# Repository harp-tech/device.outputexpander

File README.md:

## Harp Output Expander
Harp board to expand the outputs of the current harp ecosystem.

### Key Features ###

* TBA

### Connectivity ###

* TBA

## Interface ##

The interface with the Harp Output Expander can be done through [Bonsai](https://bonsai-rx.org/).

## Licensing ##

Each subdirectory will contain a license or, possibly, a set of licenses if it involves both hardware and software.

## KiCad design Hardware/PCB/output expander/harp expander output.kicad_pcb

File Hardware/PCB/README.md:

# Harp Expander PCB

## Licensing

The designs, documentation, and photos available in this repository are free: you can redistribute it and/or modify it under the terms of the used license.
Check file named LICENSE.

Copyright Filipe Carvalho 2020-2026

<br />This work is licensed under a <a rel="license" href="http://creativecommons.org/licenses/by-nc-sa/3.0/igo/">Creative Commons Attribution-NonCommercial-ShareAlike 3.0 IGO License</a>.

If your are interested in obtaining a license to sell this device, please contact filipe@open-ephys.org

[1]: https://docs.google.com/spreadsheets/d/1aobmmEzBDethzIlrm1eg0eYkBqlyX3s9WbA9KgRwVQI/edit?usp=sharing

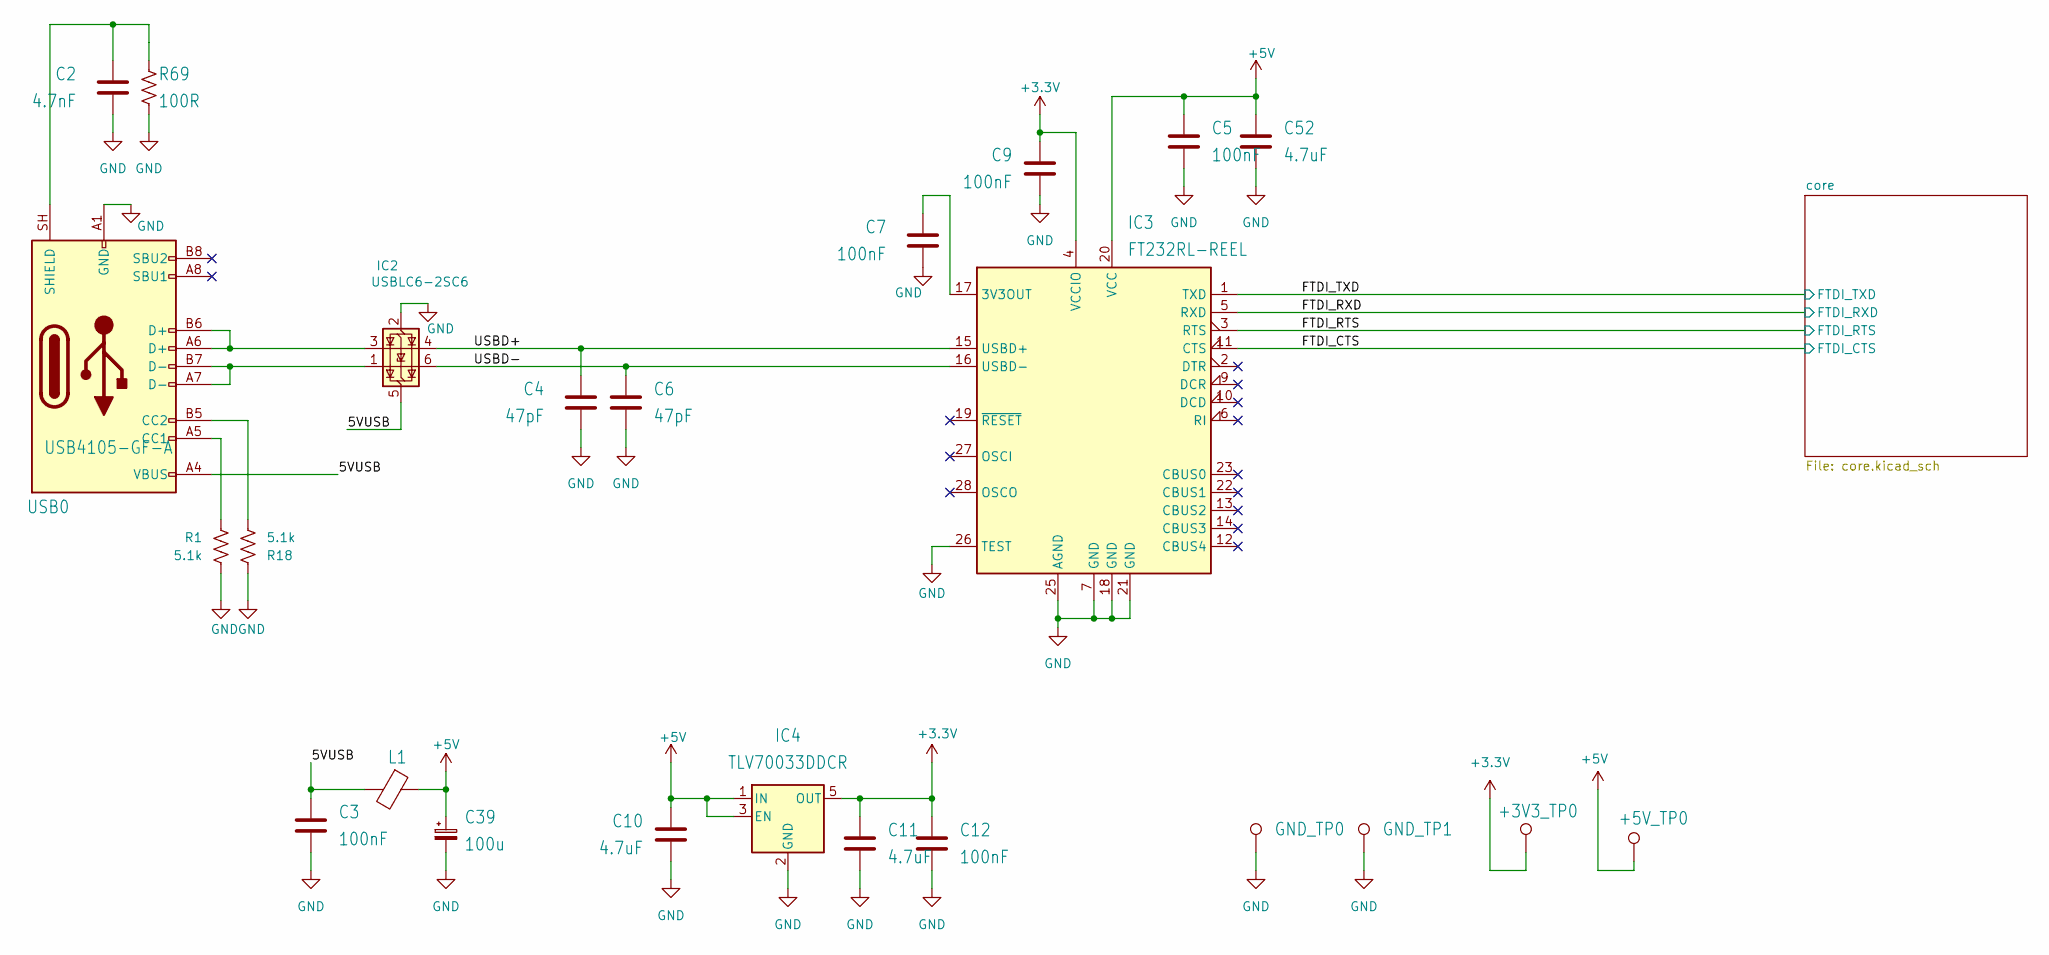
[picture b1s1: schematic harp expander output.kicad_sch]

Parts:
+3V3_TP0, +5V_TP0: TPPAD1-13; TestPoint_Loop_D1.80mm_Drill1.0mm_Beaded; MPN n.a.
C2: 4.7nF; C_0402_1005Metric; Tolerance 10%; Voltage 100V; MPN 885012205084
C3, C5, C7, C9, C12: 100nF; C_0402_1005Metric; Tolerance 10%; Voltage 50V; MPN CGA2B3X7R1H104K050BB
C4, C6: 47pF; C_0402_1005Metric; Tolerance 5%; Voltage 50V; MPN 04025A470JAT2A
C10, C11, C52: 4.7uF; C_0603_1608Metric; Tolerance 10%; Voltage 16V; MPN C1608X6S1C475K080AC
C39: 100u; CP_Radial_D6.3mm_P2.50mm; Tolerance 20%; Voltage 25V; MPN EEU-FM1E101B
GND_TP0, GND_TP1: TPPAD1-13; TestPoint_Loop_D1.80mm_Drill1.0mm_Beaded; MPN n.a.
IC2: USBLC6-2SC6; SOT-23-6; MPN USBLC6-2SC6
IC3: FT232RL-REEL; SSOP-28_5.3x10.2mm_P0.65mm; MPN FT232RL-REEL
IC4: TLV70033DDCR; SOT-23-5; MPN TLV70033DDCR
L1: MI0805K400R-10; R_0805_2012Metric; MPN MI0805K400R-10
R1, R18: 5.1k; R_0402_1005Metric; Tolerance 1%; MPN ERJ-2RKF5101X
R69: 100R; R_0603_1608Metric; Tolerance 1%; MPN CRCW0603100RFKEAHP
USB0: USB4105-GF-A; USB_C_Receptacle_GCT_USB4105-xx-A_16P_TopMnt_Horizontal; MPN USB4105-GF-A

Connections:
+3.3V: +3V3_TP0.1 (1_1), C9.1, C11.1, C12.1, IC3.4 (VCCIO), IC4.5 (OUT); also elsewhere on the board
+5V: +5V_TP0.1 (1_1), C5.1, C10.1, C39.1, C52.1, IC3.20 (VCC), IC4.1 (IN), IC4.3 (EN), L1.1; also elsewhere on the board
/5VUSB: C3.1, IC2.5 (VBUS), L1.2, USB0.A4 (VBUS), USB0.A9 (VBUS), USB0.B4 (VBUS), USB0.B9 (VBUS)
/FTDI_CTS: IC3.11 (CTS); also elsewhere on the board
/FTDI_RTS: IC3.3 (RTS); also elsewhere on the board
/FTDI_RXD: IC3.5 (RXD); also elsewhere on the board
/FTDI_TXD: IC3.1 (TXD); also elsewhere on the board
/USBD+: C4.1, IC2.4 (I/O2), IC3.15 (USBD+)
/USBD-: C6.1, IC2.6 (I/O1), IC3.16 (USBD-)
GND: C2.2, C3.2, C4.2, C5.2, C6.2, C7.2, C9.2, C10.2, C11.2, C12.2, C39.2, C52.2, GND_TP0.1 (1_1), GND_TP1.1 (1_1), IC2.2 (GND), IC3.7 (GND), IC3.18 (GND), IC3.21 (GND), IC3.25 (AGND), IC3.26 (TEST), IC4.2 (GND), R1.2, R18.1, R69.1, USB0.A1 (GND), USB0.A12 (GND), USB0.B1 (GND), USB0.B12 (GND); also elsewhere on the board
unnamed: IC2.1 (I/O1), USB0.A7 (D-), USB0.B7 (D-)
unnamed: IC2.3 (I/O2), USB0.A6 (D+), USB0.B6 (D+)
unnamed: C7.1, IC3.17 (3V3OUT)
unnamed: R1.1, USB0.A5 (CC1)
unnamed: R18.2, USB0.B5 (CC2)
unnamed: C2.1, R69.2, USB0.SH (SHIELD)

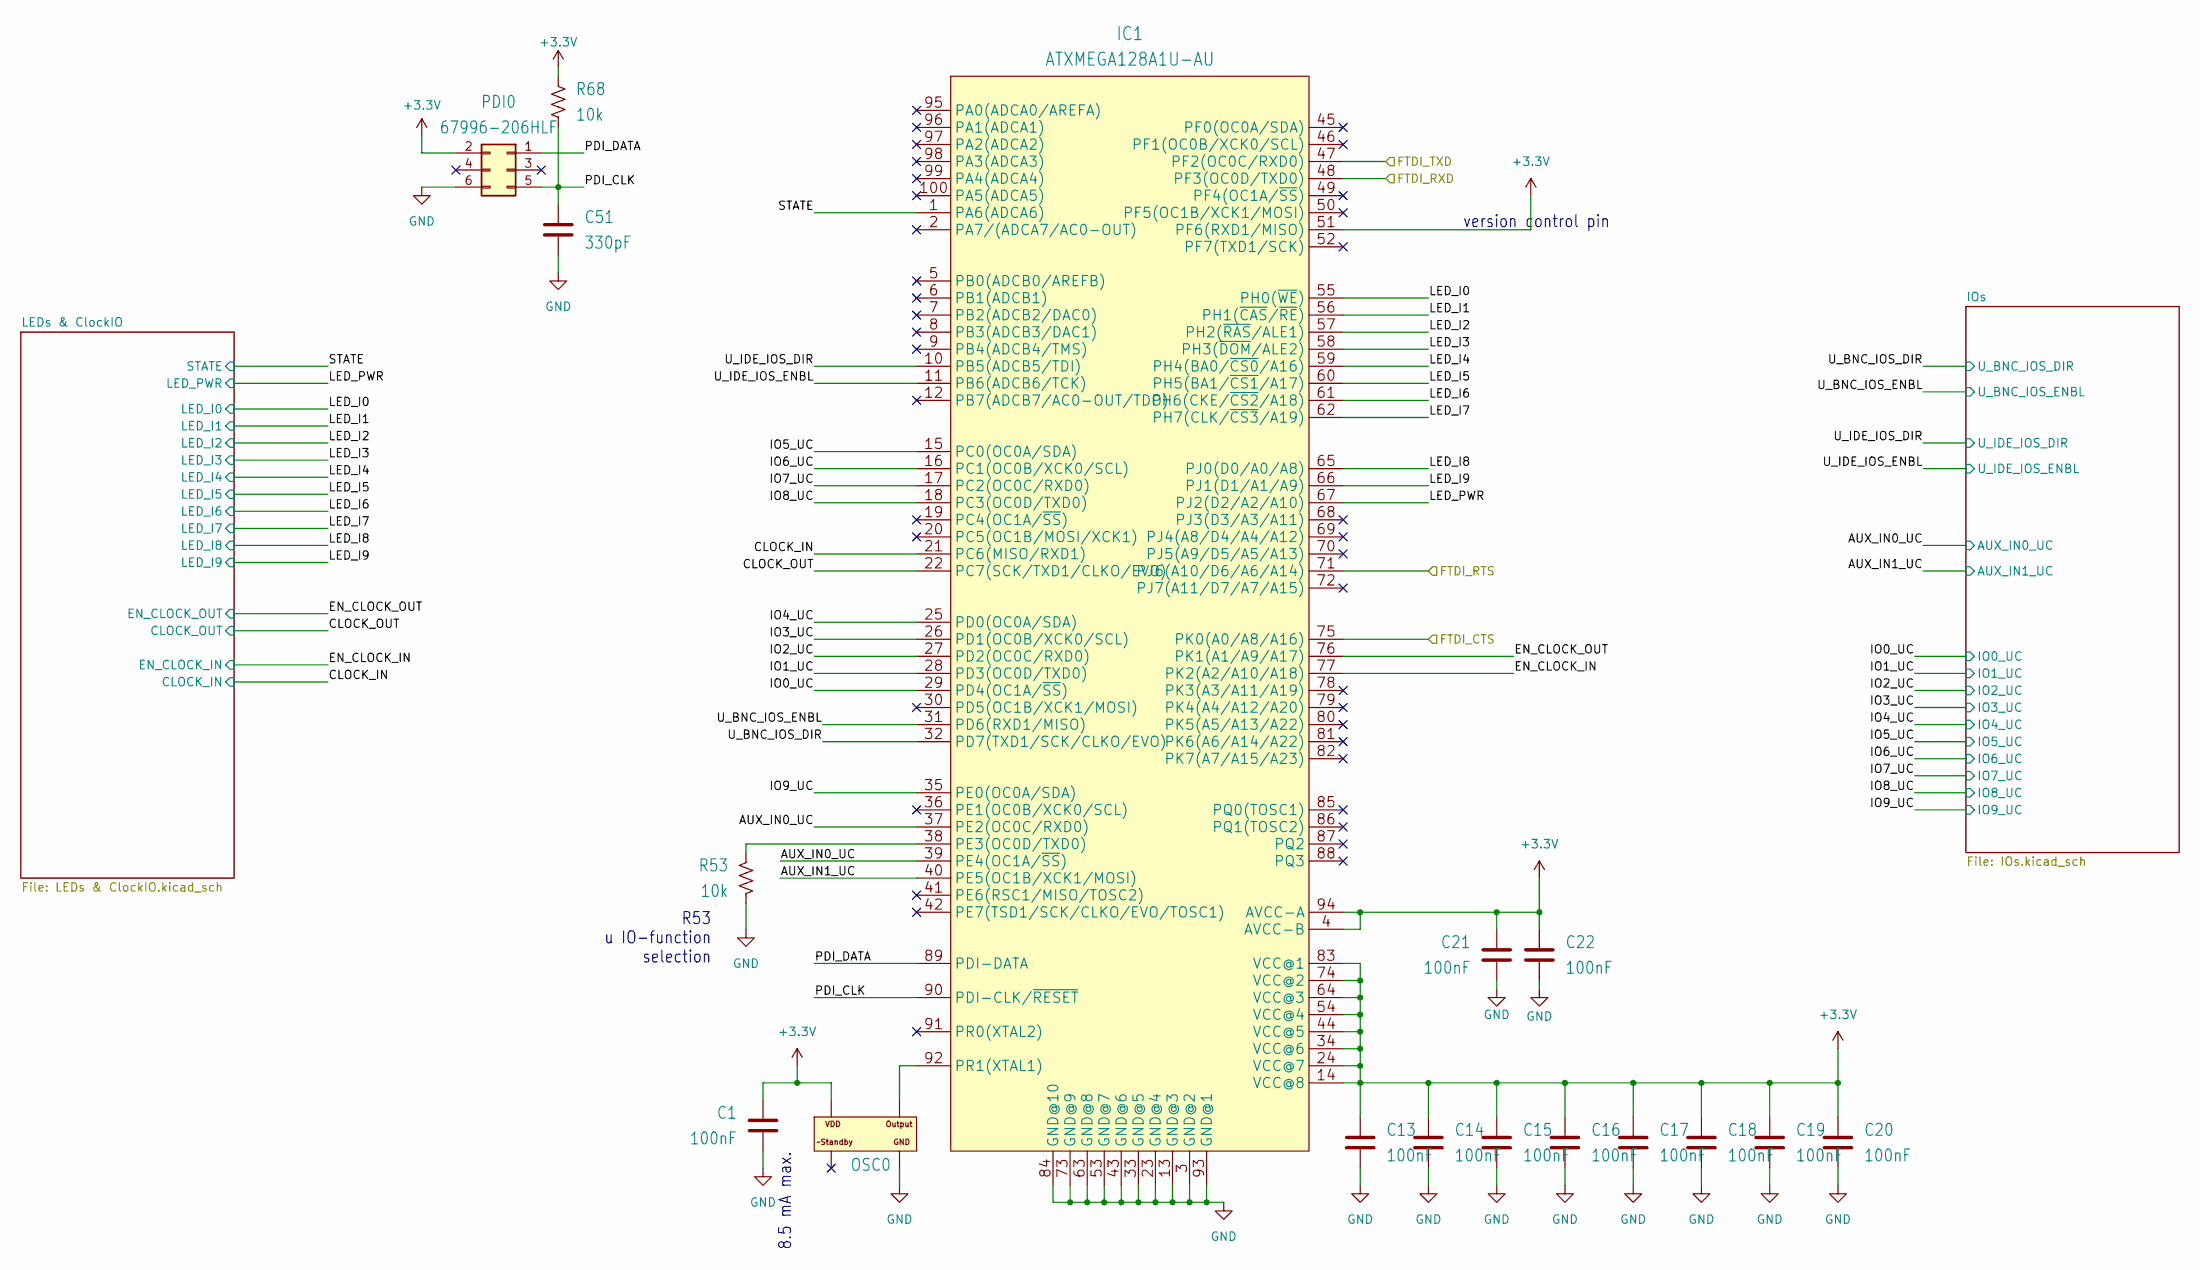
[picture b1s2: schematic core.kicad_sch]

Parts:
C1, C13, C14, C15, C16, C17, C18, C19, C20, C21, C22: 100nF; C_0402_1005Metric; Tolerance 10%; Voltage 50V; MPN CGA2B3X7R1H104K050BB
C51: 330pF; C_0402_1005Metric; Tolerance 5%; Voltage 50V; MPN C0402C331J5GAC7867
IC1: ATXMEGA128A1U-AU; TQFP-100_14x14mm_P0.5mm; MPN ATXMEGA128A1U-AU
OSC0: O 32,0-JT32C-A-K-3,3-LF; OSCILLATOR_3.2X2.5; MPN O 32,0-JT32C-A-K-3,3-LF
PDI0: 67996-206HLF; PinHeader_2x03_P2.54mm_Vertical; MPN 67996-206HLF
R53, R68: 10k; R_0402_1005Metric; Tolerance 1%; MPN CRCW040210K0FKED

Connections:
+3.3V: C1.1, C13.1, C14.1, C15.1, C16.1, C17.1, C18.1, C19.1, C20.1, C21.1, C22.1, IC1.4 (AVCC-B), IC1.14 (VCC@8), IC1.24 (VCC@7), IC1.34 (VCC@6), IC1.44 (VCC@5), IC1.51 (PF6(RXD1/MISO)), IC1.54 (VCC@4), IC1.64 (VCC@3), IC1.74 (VCC@2), IC1.83 (VCC@1), IC1.94 (AVCC-A), OSC0.4 (VDD), PDI0.2, R68.2; also elsewhere on the board
/FTDI_CTS: IC1.75 (PK0(A0/A8/A16)); also elsewhere on the board
/FTDI_RTS: IC1.71 (PJ6(A10/D6/A6/A14)); also elsewhere on the board
/FTDI_RXD: IC1.48 (PF3(OC0D/TXD0)); also elsewhere on the board
/FTDI_TXD: IC1.47 (PF2(OC0C/RXD0)); also elsewhere on the board
/core/AUX_IN0_UC: IC1.37 (PE2(OC0C/RXD0)), IC1.39 (PE4(OC1A/~SS)); also elsewhere on the board
/core/AUX_IN1_UC: IC1.40 (PE5(OC1B/XCK1/MOSI)); also elsewhere on the board
/core/CLOCK_IN: IC1.21 (PC6(MISO/RXD1)); also elsewhere on the board
/core/CLOCK_OUT: IC1.22 (PC7(SCK/TXD1/CLKO/EVO)); also elsewhere on the board
/core/EN_CLOCK_IN: IC1.77 (PK2(A2/A10/A18)); also elsewhere on the board
/core/EN_CLOCK_OUT: IC1.76 (PK1(A1/A9/A17)); also elsewhere on the board
/core/IO0_UC: IC1.29 (PD4(OC1A/~SS)); also elsewhere on the board
/core/IO1_UC: IC1.28 (PD3(OC0D/TXD0)); also elsewhere on the board
/core/IO2_UC: IC1.27 (PD2(OC0C/RXD0)); also elsewhere on the board
/core/IO3_UC: IC1.26 (PD1(OC0B/XCK0/SCL)); also elsewhere on the board
/core/IO4_UC: IC1.25 (PD0(OC0A/SDA)); also elsewhere on the board
/core/IO5_UC: IC1.15 (PC0(OC0A/SDA)); also elsewhere on the board
/core/IO6_UC: IC1.16 (PC1(OC0B/XCK0/SCL)); also elsewhere on the board
/core/IO7_UC: IC1.17 (PC2(OC0C/RXD0)); also elsewhere on the board
/core/IO8_UC: IC1.18 (PC3(OC0D/TXD0)); also elsewhere on the board
/core/IO9_UC: IC1.35 (PE0(OC0A/SDA)); also elsewhere on the board
/core/LED_I0: IC1.55 (PH0(~WE)); also elsewhere on the board
/core/LED_I1: IC1.56 (PH1(~CAS/~RE)); also elsewhere on the board
/core/LED_I2: IC1.57 (PH2(~RAS/ALE1)); also elsewhere on the board
/core/LED_I3: IC1.58 (PH3(~DOM/ALE2)); also elsewhere on the board
/core/LED_I4: IC1.59 (PH4(BA0/~CS0/A16)); also elsewhere on the board
/core/LED_I5: IC1.60 (PH5(BA1/~CS1/A17)); also elsewhere on the board
/core/LED_I6: IC1.61 (PH6(CKE/~CS2/A18)); also elsewhere on the board
/core/LED_I7: IC1.62 (PH7(CLK/~CS3/A19)); also elsewhere on the board
/core/LED_I8: IC1.65 (PJ0(D0/A0/A8)); also elsewhere on the board
/core/LED_I9: IC1.66 (PJ1(D1/A1/A9)); also elsewhere on the board
/core/LED_PWR: IC1.67 (PJ2(D2/A2/A10)); also elsewhere on the board
/core/PDI_CLK: C51.1, IC1.90 (PDI-CLK/~RESET), PDI0.5, R68.1
/core/PDI_DATA: IC1.89 (PDI-DATA), PDI0.1
/core/STATE: IC1.1 (PA6(ADCA6)); also elsewhere on the board
/core/U_BNC_IOS_DIR: IC1.32 (PD7(TXD1/SCK/CLKO/EVO)); also elsewhere on the board
/core/U_BNC_IOS_ENBL: IC1.31 (PD6(RXD1/MISO)); also elsewhere on the board
/core/U_IDE_IOS_DIR: IC1.10 (PB5(ADCB5/TDI)); also elsewhere on the board
/core/U_IDE_IOS_ENBL: IC1.11 (PB6(ADCB6/TCK)); also elsewhere on the board
GND: C1.2, C13.2, C14.2, C15.2, C16.2, C17.2, C18.2, C19.2, C20.2, C21.2, C22.2, C51.2, IC1.3 (GND@2), IC1.13 (GND@3), IC1.23 (GND@4), IC1.33 (GND@5), IC1.43 (GND@6), IC1.53 (GND@7), IC1.63 (GND@8), IC1.73 (GND@9), IC1.84 (GND@10), IC1.93 (GND@1), OSC0.2 (GND), PDI0.6, R53.2; also elsewhere on the board
unnamed: IC1.38 (PE3(OC0D/TXD0)), R53.1
unnamed: IC1.92 (PR1(XTAL1)), OSC0.3 (OUTPUT)

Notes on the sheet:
8.5 mA max.
R53 u IO-function selection
version control pin

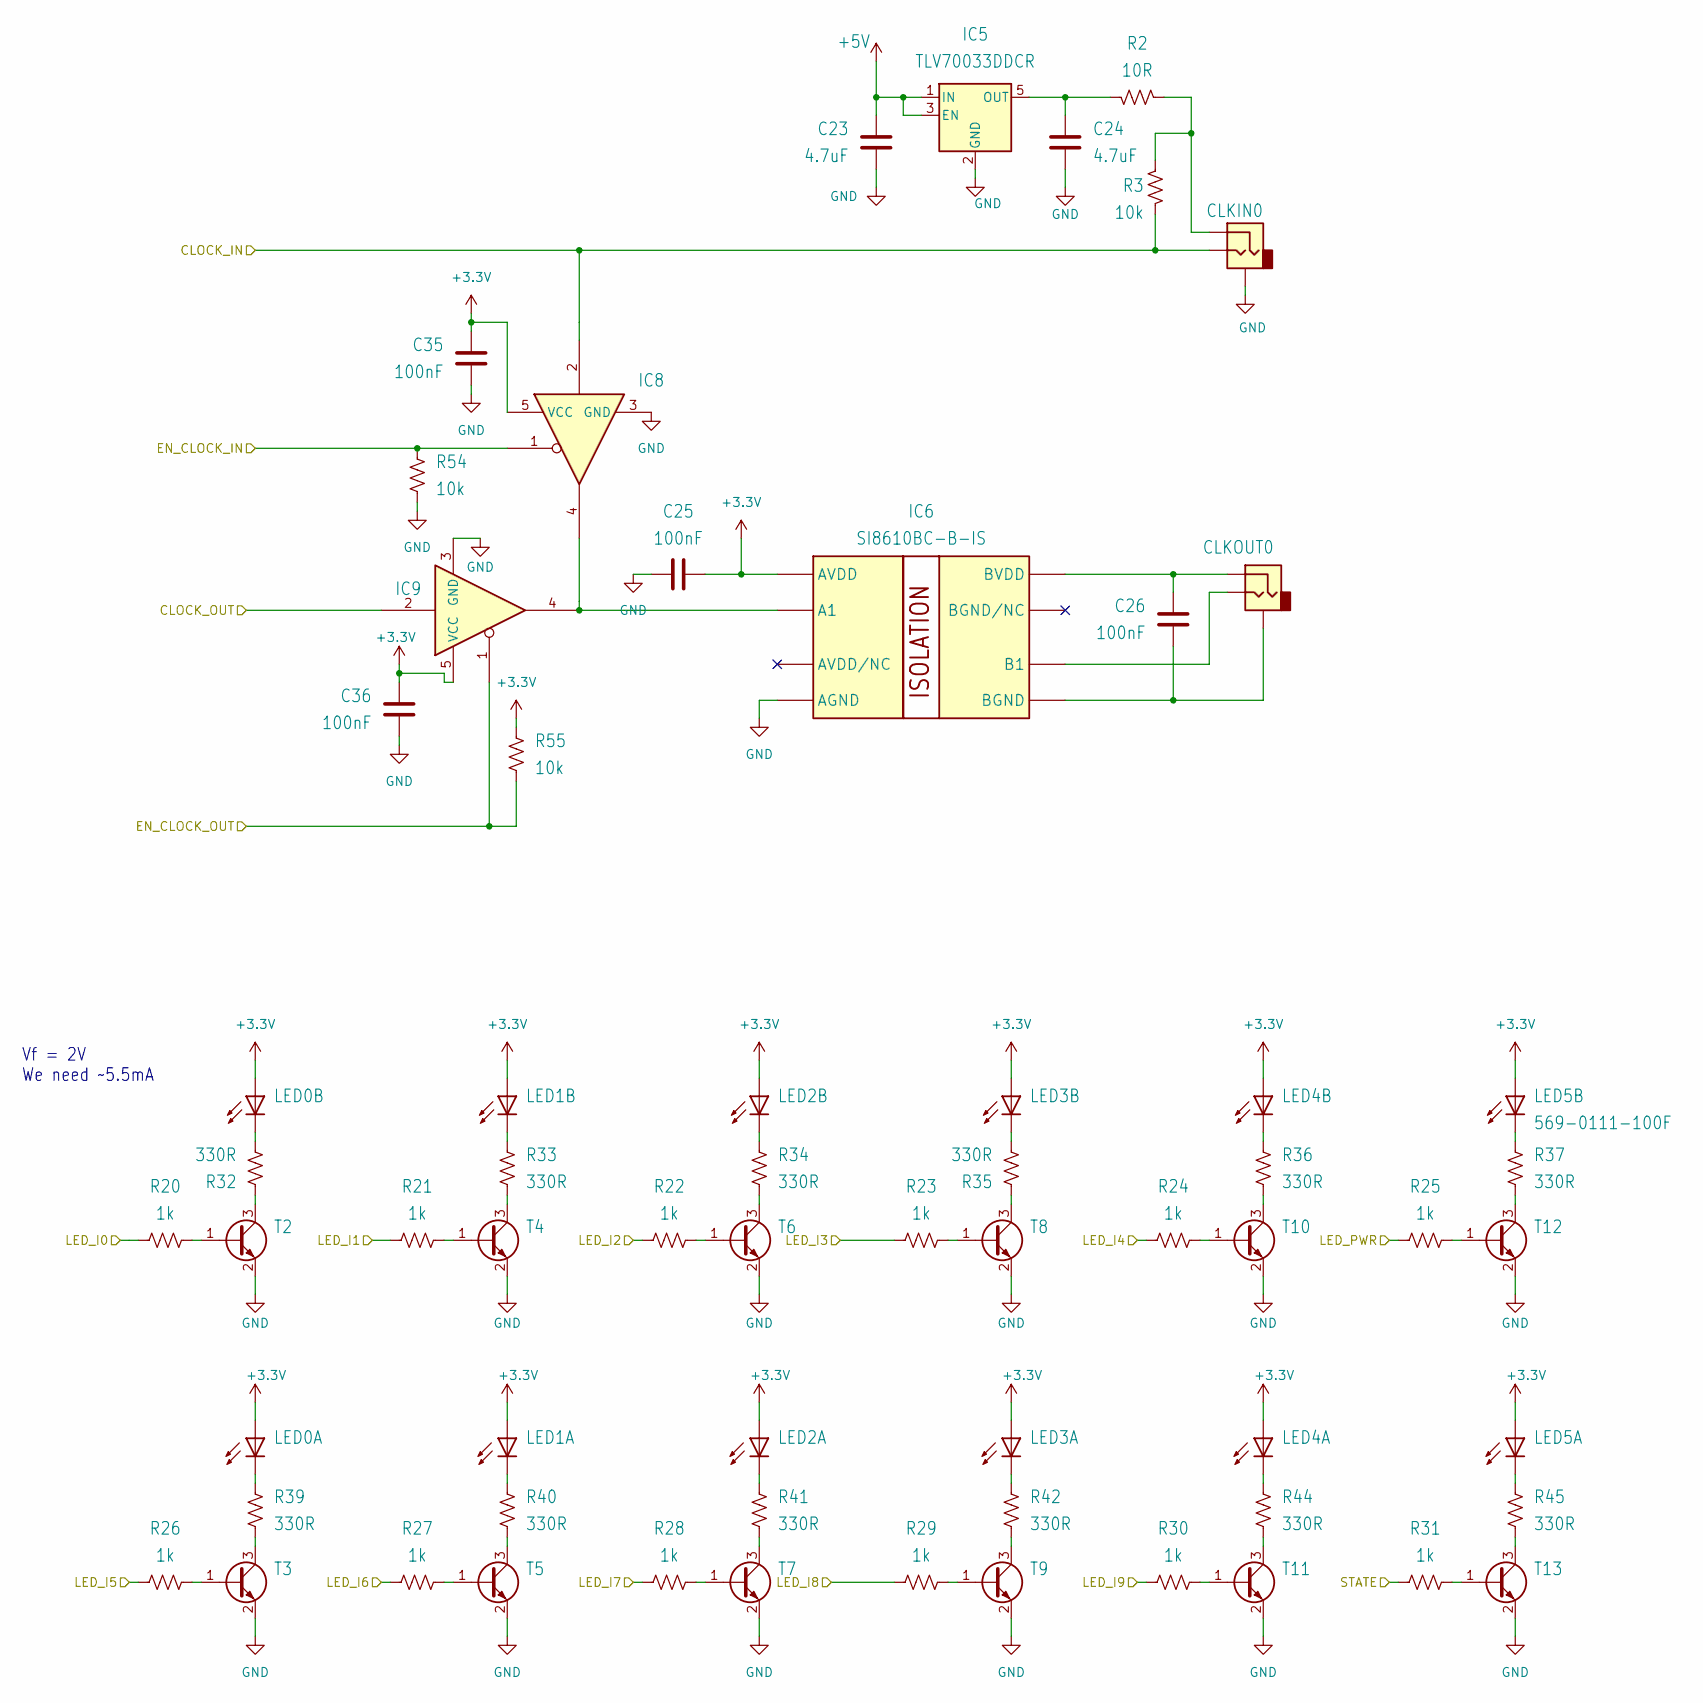
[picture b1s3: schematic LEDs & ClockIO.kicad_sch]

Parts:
C23, C24: 4.7uF; C_0603_1608Metric; Tolerance 10%; Voltage 16V; MPN C1608X6S1C475K080AC
C25, C26, C35, C36: 100nF; C_0402_1005Metric; Tolerance 10%; Voltage 50V; MPN CGA2B3X7R1H104K050BB
CLKIN0: 35RASMT2BHNTRX; MPN 35RASMT2BHNTRX
CLKOUT0: 35RASMT2BHNTRX; MPN 35RASMT2BHNTRX
IC5: TLV70033DDCR; SOT-23-5; MPN TLV70033DDCR
IC6: SI8610BC-B-IS; SOIC-8_3.9x4.9mm_P1.27mm; MPN SI8610BC-B-ISR
IC8, IC9: SN74LVC1G125DBVT; SOT-23-5; MPN SN74LVC1G125DBVT
LED0, LED1, LED2, LED3, LED4, LED5: 569-0111-100F; 569-011X-X00_LED_ARRAY; MPN 569-0111-100F
R2: 10R; R_0402_1005Metric; Tolerance 5%; MPN ERJ-PA2J100X
R3, R54, R55: 10k; R_0402_1005Metric; Tolerance 1%; MPN CRCW040210K0FKED
R20, R21, R22, R23, R24, R25, R26, R27, R28, R29, R30, R31: 1k; R_0402_1005Metric; Tolerance 1%; MPN CRCW04021K00FKED
R32, R33, R34, R35, R36, R37, R39, R40, R41, R42, R44, R45: 330R; R_0402_1005Metric; Tolerance 1%; MPN RC0402FR-07330RL
T2, T3, T4, T5, T6, T7, T8, T9, T10, T11, T12, T13: BC850C,215; SOT-23; MPN BC850C,215

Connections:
+3.3V: C25.1, C35.1, C36.1, IC6.1 (AVDD), IC8.5 (VCC), IC9.5 (VCC), LED0.A1 (A), LED0.A2 (A), LED1.A1 (A), LED1.A2 (A), LED2.A1 (A), LED2.A2 (A), LED3.A1 (A), LED3.A2 (A), LED4.A1 (A), LED4.A2 (A), LED5.A1 (A), LED5.A2 (A), R55.2; also elsewhere on the board
+5V: C23.1, IC5.1 (IN), IC5.3 (EN); also elsewhere on the board
/core/CLOCK_IN: CLKIN0.2, IC8.2, R3.1; also elsewhere on the board
/core/CLOCK_OUT: IC9.2; also elsewhere on the board
/core/EN_CLOCK_IN: IC8.1, R54.1; also elsewhere on the board
/core/EN_CLOCK_OUT: IC9.1, R55.1; also elsewhere on the board
/core/LED_I0: R20.1; also elsewhere on the board
/core/LED_I1: R21.1; also elsewhere on the board
/core/LED_I2: R22.1; also elsewhere on the board
/core/LED_I3: R23.1; also elsewhere on the board
/core/LED_I4: R24.1; also elsewhere on the board
/core/LED_I5: R26.1; also elsewhere on the board
/core/LED_I6: R27.1; also elsewhere on the board
/core/LED_I7: R28.1; also elsewhere on the board
/core/LED_I8: R29.1; also elsewhere on the board
/core/LED_I9: R30.1; also elsewhere on the board
/core/LED_PWR: R25.1; also elsewhere on the board
/core/STATE: R31.1; also elsewhere on the board
GND: C23.2, C24.2, C25.2, C35.2, C36.2, CLKIN0.1, IC5.2 (GND), IC6.4 (AGND), IC8.3 (GND), IC9.3 (GND), R54.2, T2.2 (E), T3.2 (E), T4.2 (E), T5.2 (E), T6.2 (E), T7.2 (E), T8.2 (E), T9.2 (E), T10.2 (E), T11.2 (E), T12.2 (E), T13.2 (E); also elsewhere on the board
unnamed: CLKIN0.3, R2.1, R3.2
unnamed: C24.1, IC5.5 (OUT), R2.2
unnamed: IC6.2 (A1), IC8.4, IC9.4
unnamed: CLKOUT0.2, IC6.6 (B1)
unnamed: C26.2, CLKOUT0.1, IC6.5 (BGND)
unnamed: C26.1, CLKOUT0.3, IC6.8 (BVDD)
unnamed: LED0.C1 (C), R39.1
unnamed: LED0.C2 (C), R32.1
unnamed: LED1.C1 (C), R40.1
unnamed: LED1.C2 (C), R33.1
unnamed: LED2.C1 (C), R41.1
unnamed: LED2.C2 (C), R34.1
unnamed: LED3.C1 (C), R42.1
unnamed: LED3.C2 (C), R35.1
unnamed: LED4.C1 (C), R44.1
unnamed: LED4.C2 (C), R36.1
unnamed: LED5.C1 (C), R45.1
unnamed: LED5.C2 (C), R37.1
unnamed: R20.2, T2.1 (B)
unnamed: R32.2, T2.3 (C)
unnamed: R26.2, T3.1 (B)
unnamed: R39.2, T3.3 (C)
unnamed: R21.2, T4.1 (B)
unnamed: R33.2, T4.3 (C)
unnamed: R27.2, T5.1 (B)
unnamed: R40.2, T5.3 (C)
unnamed: R22.2, T6.1 (B)
unnamed: R34.2, T6.3 (C)
unnamed: R28.2, T7.1 (B)
unnamed: R41.2, T7.3 (C)
unnamed: R23.2, T8.1 (B)
unnamed: R35.2, T8.3 (C)
unnamed: R29.2, T9.1 (B)
unnamed: R42.2, T9.3 (C)
unnamed: R24.2, T10.1 (B)
unnamed: R36.2, T10.3 (C)
unnamed: R30.2, T11.1 (B)
unnamed: R44.2, T11.3 (C)
unnamed: R25.2, T12.1 (B)
unnamed: R37.2, T12.3 (C)
unnamed: R31.2, T13.1 (B)
unnamed: R45.2, T13.3 (C)

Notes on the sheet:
Vf = 2V We need ~5.5mA

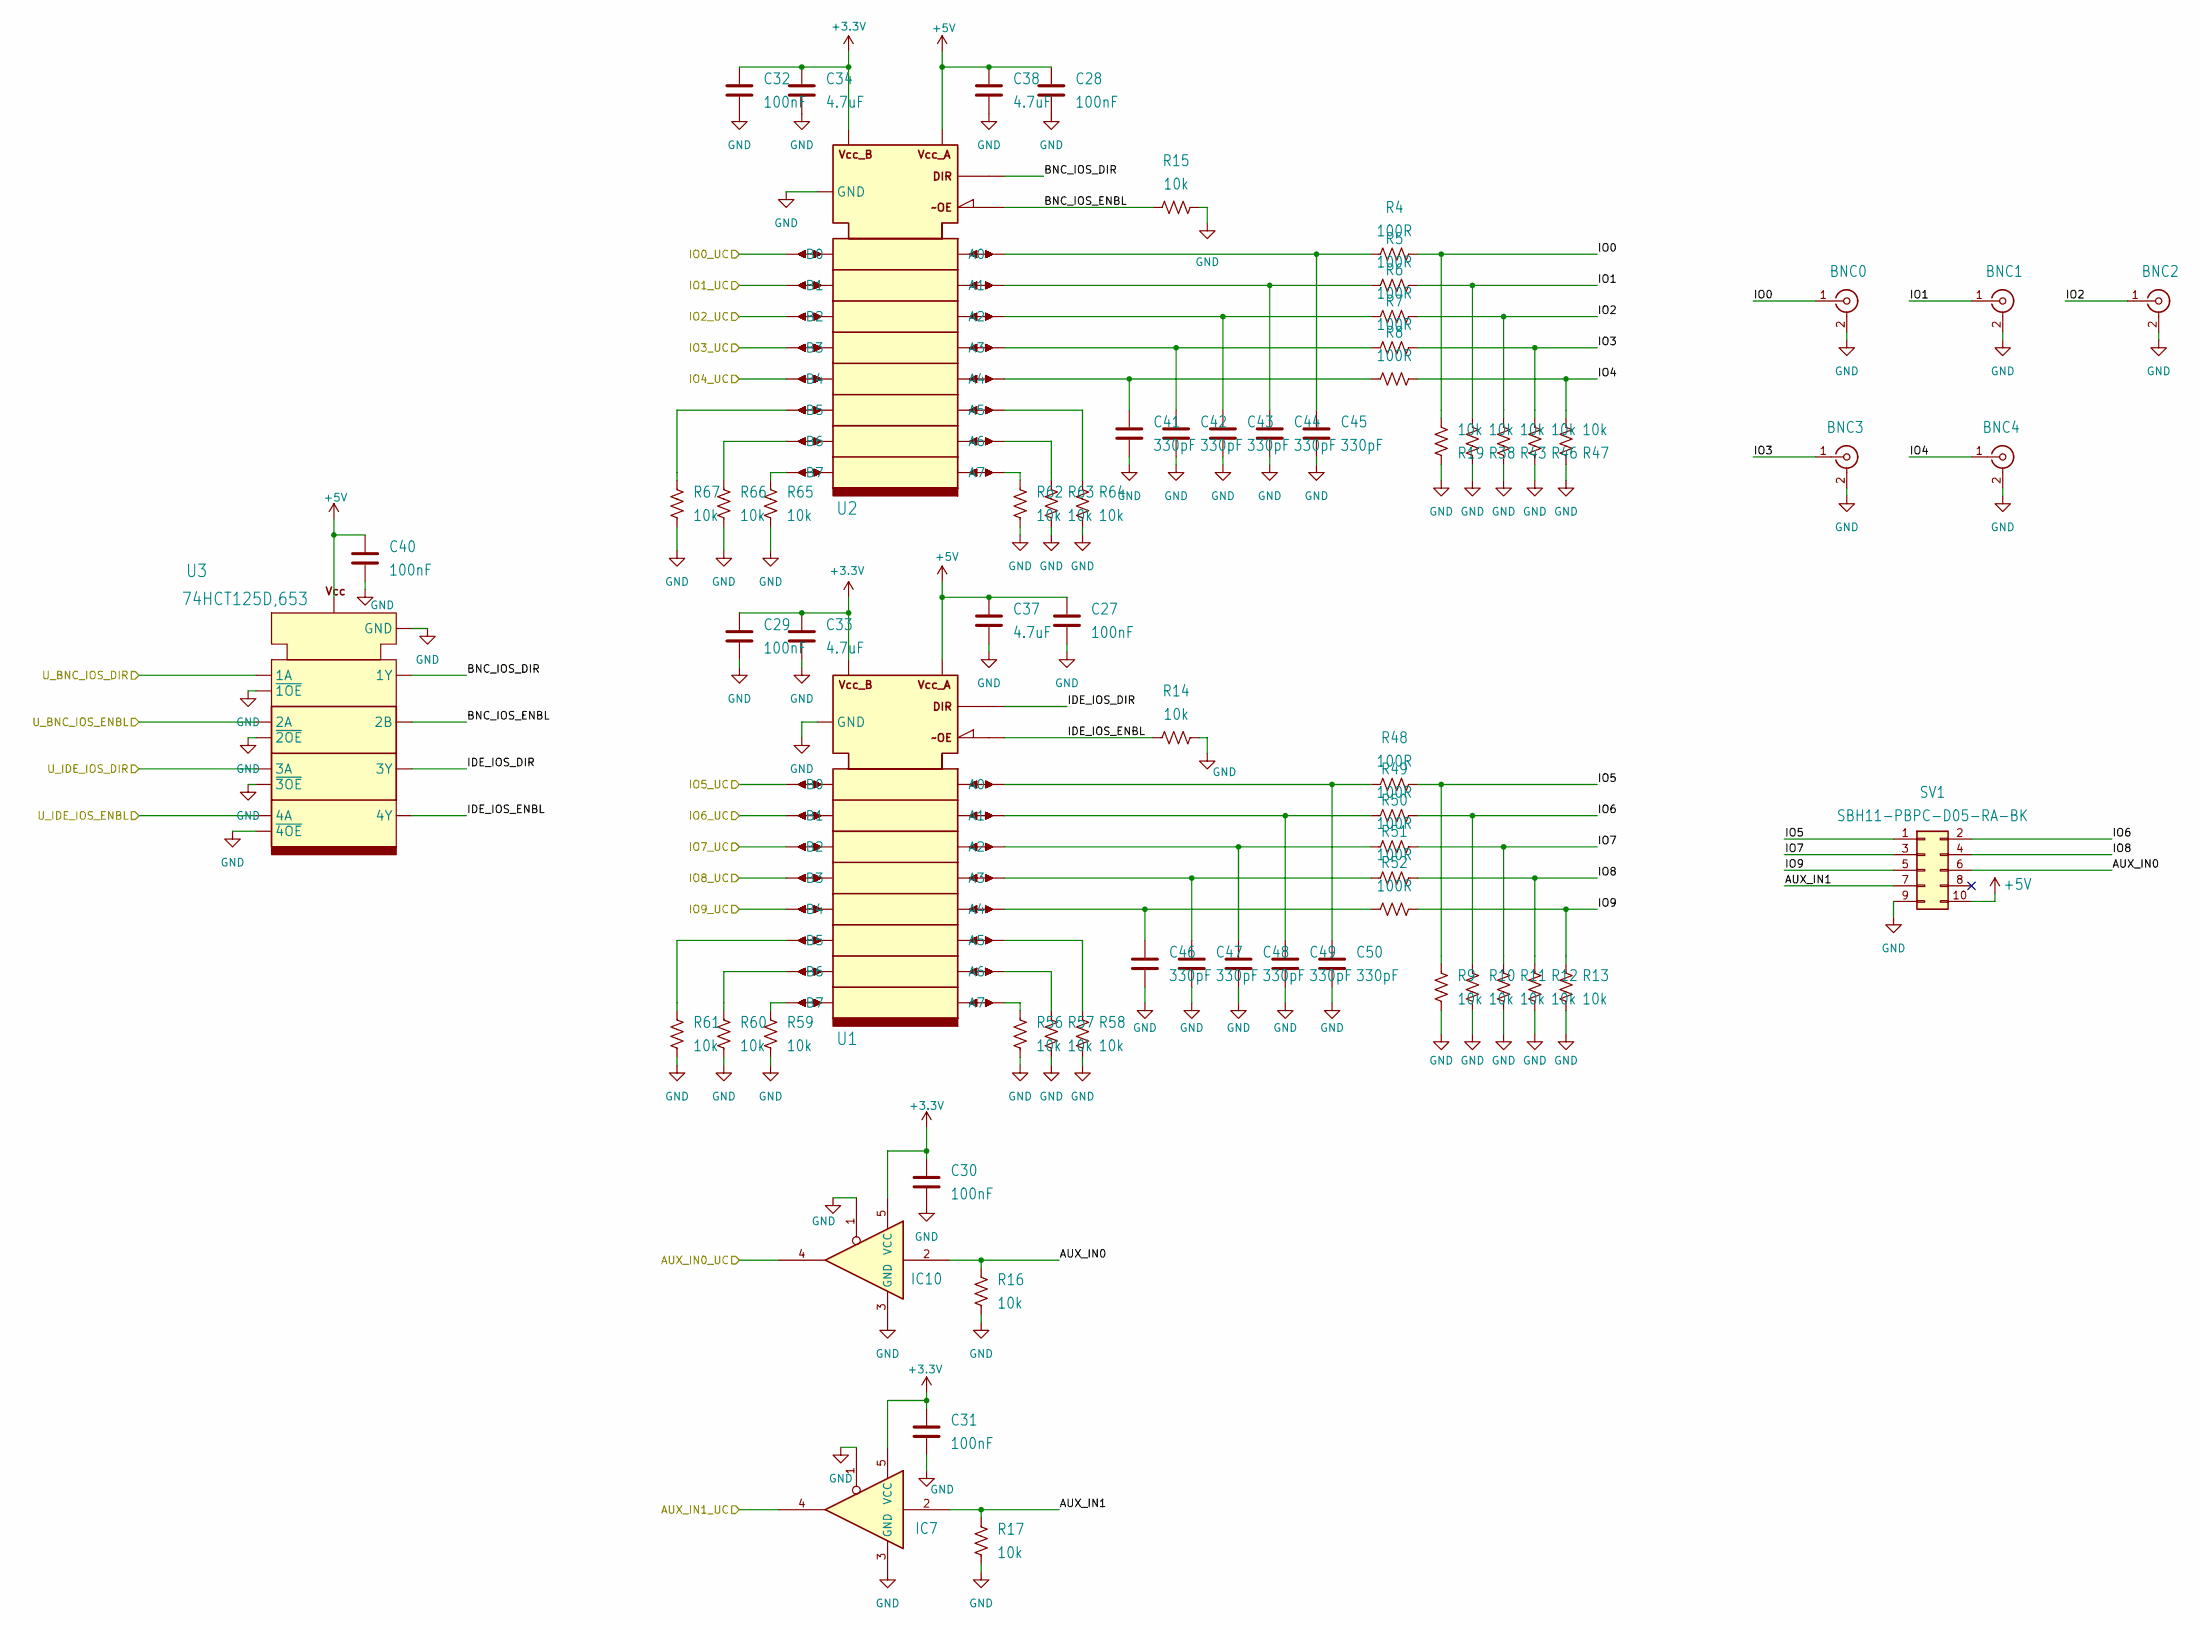
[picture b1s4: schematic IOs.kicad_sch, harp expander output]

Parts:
BNC0, BNC1, BNC2, BNC3, BNC4: 731000105; BNC_MOLEX_0731000105; MPN 0731000105
C27, C28, C29, C30, C31, C32, C40: 100nF; C_0402_1005Metric; Tolerance 10%; Voltage 50V; MPN CGA2B3X7R1H104K050BB
C33, C34, C37, C38: 4.7uF; C_0603_1608Metric; Tolerance 10%; Voltage 16V; MPN C1608X6S1C475K080AC
C41, C42, C43, C44, C45, C46, C47, C48, C49, C50: 330pF; C_0402_1005Metric; Tolerance 5%; Voltage 50V; MPN C0402C331J5GAC7867
IC7, IC10: SN74LVC1G125DBVT; SOT-23-5; MPN SN74LVC1G125DBVT
R4, R5, R6, R7, R8, R48, R49, R50, R51, R52: 100R; R_0603_1608Metric; Tolerance 1%; MPN CRCW0603100RFKEAHP
R9, R10, R11, R12, R13, R14, R15, R16, R17, R19, R38, R43, R46, R47, R56, R57, R58, R59, R60, R61, R62, R63, R64, R65, R66, R67: 10k; R_0402_1005Metric; Tolerance 1%; MPN CRCW040210K0FKED
SV1: SBH11-PBPC-D05-RA-BK; IDC-Header_2x05_P2.54mm_Horizontal; MPN SBH11-PBPC-D05-RA-BK
U1, U2: SN74LVC8T245DWR; SOIC-24W_7.5x15.4mm_P1.27mm; MPN SN74LVC8T245DWR
U3: 74HCT125D,653; SO-14_5.3x10.2mm_P1.27mm; MPN 74HCT125D,653

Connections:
+3.3V: C29.1, C30.1, C31.1, C32.1, C33.1, C34.1, IC7.5 (VCC), IC10.5 (VCC), U1.23 (VCC_B), U1.24 (VCC_B), U2.23 (VCC_B), U2.24 (VCC_B); also elsewhere on the board
+5V: C27.1, C28.1, C37.1, C38.1, C40.1, SV1.10, U1.1 (VCC_A), U2.1 (VCC_A), U3.14 (VCC); also elsewhere on the board
/core/AUX_IN0_UC: IC10.4; also elsewhere on the board
/core/AUX_IN1_UC: IC7.4; also elsewhere on the board
/core/IO0_UC: U2.21 (B0); also elsewhere on the board
/core/IO1_UC: U2.20 (B1); also elsewhere on the board
/core/IO2_UC: U2.19 (B2); also elsewhere on the board
/core/IO3_UC: U2.18 (B3); also elsewhere on the board
/core/IO4_UC: U2.17 (B4); also elsewhere on the board
/core/IO5_UC: U1.21 (B0); also elsewhere on the board
/core/IO6_UC: U1.20 (B1); also elsewhere on the board
/core/IO7_UC: U1.19 (B2); also elsewhere on the board
/core/IO8_UC: U1.18 (B3); also elsewhere on the board
/core/IO9_UC: U1.17 (B4); also elsewhere on the board
/core/IOs/AUX_IN0: IC10.2, R16.1, SV1.6
/core/IOs/AUX_IN1: IC7.2, R17.1, SV1.7
/core/IOs/BNC_IOS_DIR: U2.2 (DIR), U3.3 (1Y)
/core/IOs/BNC_IOS_ENBL: R15.2, U2.22 (OE), U3.6 (2B)
/core/IOs/IDE_IOS_DIR: U1.2 (DIR), U3.8 (3Y)
/core/IOs/IDE_IOS_ENBL: R14.2, U1.22 (OE), U3.11 (4Y)
/core/IOs/IO0: BNC0.1 (In), R4.1, R19.2
/core/IOs/IO1: BNC1.1 (In), R5.1, R38.2
/core/IOs/IO2: BNC2.1 (In), R6.1, R43.2
/core/IOs/IO3: BNC3.1 (In), R7.1, R46.2
/core/IOs/IO4: BNC4.1 (In), R8.1, R47.2
/core/IOs/IO5: R9.1, R48.1, SV1.1
/core/IOs/IO6: R10.1, R49.1, SV1.2
/core/IOs/IO7: R11.1, R50.1, SV1.3
/core/IOs/IO8: R12.1, R51.1, SV1.4
/core/IOs/IO9: R13.1, R52.1, SV1.5
/core/U_BNC_IOS_DIR: U3.2 (1A); also elsewhere on the board
/core/U_BNC_IOS_ENBL: U3.5 (2A); also elsewhere on the board
/core/U_IDE_IOS_DIR: U3.9 (3A); also elsewhere on the board
/core/U_IDE_IOS_ENBL: U3.12 (4A); also elsewhere on the board
GND: BNC0.2 (Ext), BNC1.2 (Ext), BNC2.2 (Ext), BNC3.2 (Ext), BNC4.2 (Ext), C27.2, C28.2, C29.2, C30.2, C31.2, C32.2, C33.2, C34.2, C37.2, C38.2, C40.2, C41.2, C42.2, C43.2, C44.2, C45.2, C46.2, C47.2, C48.2, C49.2, C50.2, IC7.1, IC7.3 (GND), IC10.1, IC10.3 (GND), R9.2, R10.2, R11.2, R12.2, R13.2, R14.1, R15.1, R16.2, R17.2, R19.1, R38.1, R43.1, R46.1, R47.1, R56.2, R57.2, R58.2, R59.2, R60.2, R61.2, R62.2, R63.2, R64.2, R65.2, R66.2, R67.2, SV1.9, U1.11 (GND), U1.12 (GND), U1.13 (GND), U2.11 (GND), U2.12 (GND), U2.13 (GND), U3.1 (~1OE), U3.4 (~2OE), U3.7 (GND), U3.10 (~3OE), U3.13 (~4OE); also elsewhere on the board
unnamed: C50.1, R48.2, U1.3 (A0)
unnamed: C49.1, R49.2, U1.4 (A1)
unnamed: C48.1, R50.2, U1.5 (A2)
unnamed: C47.1, R51.2, U1.6 (A3)
unnamed: C46.1, R52.2, U1.7 (A4)
unnamed: R58.1, U1.8 (A5)
unnamed: R57.1, U1.9 (A6)
unnamed: R56.1, U1.10 (A7)
unnamed: R61.1, U1.16 (B5)
unnamed: R60.1, U1.15 (B6)
unnamed: R59.1, U1.14 (B7)
unnamed: C45.1, R4.2, U2.3 (A0)
unnamed: C44.1, R5.2, U2.4 (A1)
unnamed: C43.1, R6.2, U2.5 (A2)
unnamed: C42.1, R7.2, U2.6 (A3)
unnamed: C41.1, R8.2, U2.7 (A4)
unnamed: R64.1, U2.8 (A5)
unnamed: R63.1, U2.9 (A6)
unnamed: R62.1, U2.10 (A7)
unnamed: R67.1, U2.16 (B5)
unnamed: R66.1, U2.15 (B6)
unnamed: R65.1, U2.14 (B7)
